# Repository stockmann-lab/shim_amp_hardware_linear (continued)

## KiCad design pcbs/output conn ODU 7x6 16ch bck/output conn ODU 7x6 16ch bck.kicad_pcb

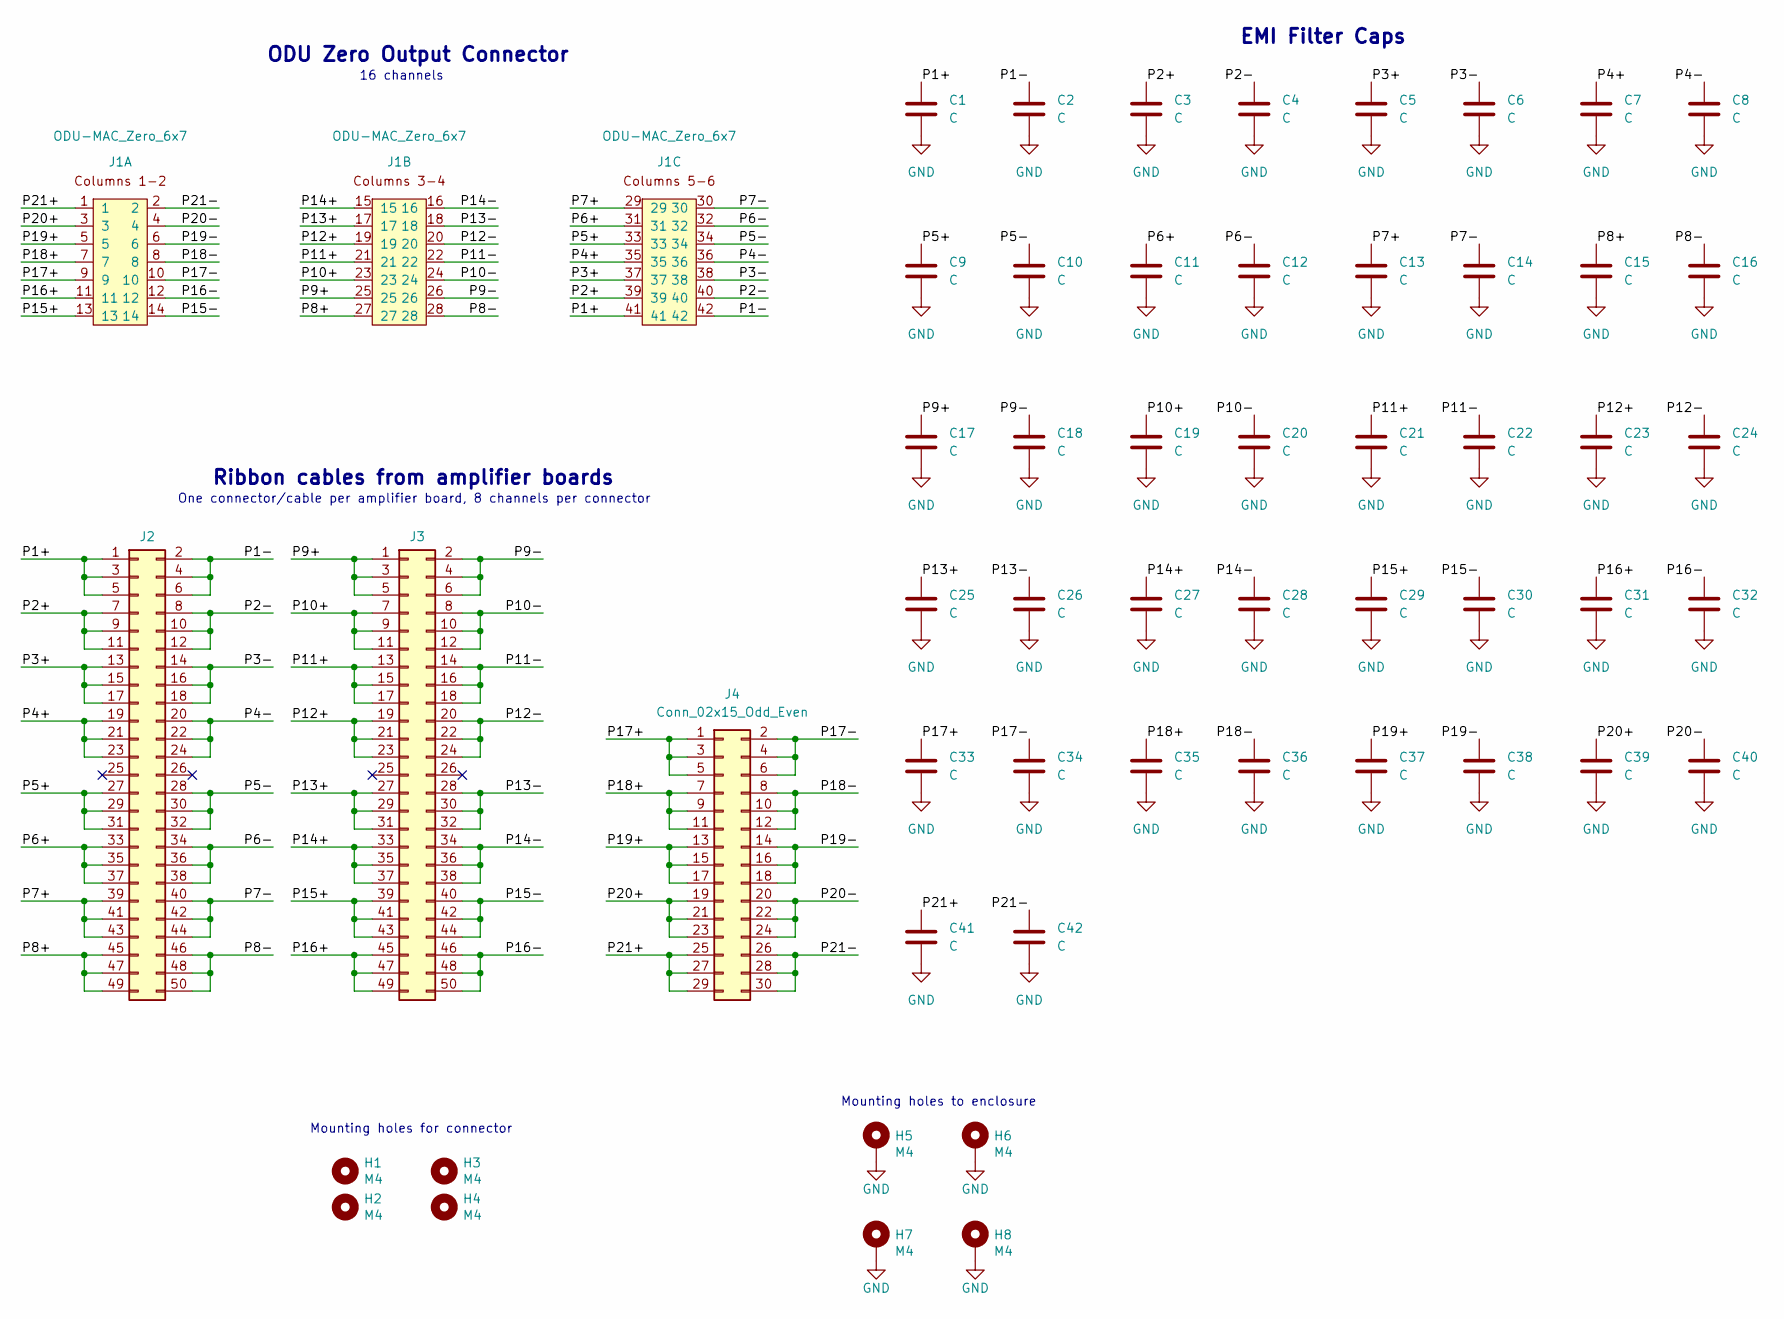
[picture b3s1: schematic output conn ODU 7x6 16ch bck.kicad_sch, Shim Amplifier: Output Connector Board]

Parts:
C1, C2, C3, C4, C5, C6, C7, C8, C9, C10, C11, C12, C13, C14, C15, C16, C17, C18, C19, C20, C21, C22, C23, C24, C25, C26, C27, C28, C29, C30, C31, C32, C33, C34, C35, C36, C37, C38, C39, C40, C41, C42: C; C_0603_1608Metric
H1, H2, H3, H4: M4; MountingHole_4.3mm_M4
H5, H6, H7, H8: M4; MountingHole_4.3mm_M4_Pad_Via
J1: ODU-MAC_Zero_6x7; ODU-MAC_Zero_6x7_bck
J2, J3: Conn_02x25_Odd_Even; PinHeader_2x25_P2.54mm_Vertical_Shrouded
J4: Conn_02x15_Odd_Even; PinHeader_2x15_P2.54mm_Vertical_Shrouded

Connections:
/P1+: C1.1, J1.41, J2.1, J2.3, J2.5
/P1-: C2.1, J1.42, J2.2, J2.4, J2.6
/P2+: C3.1, J1.39, J2.7, J2.9, J2.11
/P2-: C4.1, J1.40, J2.8, J2.10, J2.12
/P3+: C5.1, J1.37, J2.13, J2.15, J2.17
/P3-: C6.1, J1.38, J2.14, J2.16, J2.18
/P4+: C7.1, J1.35, J2.19, J2.21, J2.23
/P4-: C8.1, J1.36, J2.20, J2.22, J2.24
/P5+: C9.1, J1.33, J2.27, J2.29, J2.31
/P5-: C10.1, J1.34, J2.28, J2.30, J2.32
/P6+: C11.1, J1.31, J2.33, J2.35, J2.37
/P6-: C12.1, J1.32, J2.34, J2.36, J2.38
/P7+: C13.1, J1.29, J2.39, J2.41, J2.43
/P7-: C14.1, J1.30, J2.40, J2.42, J2.44
/P8+: C15.1, J1.27, J2.45, J2.47, J2.49
/P8-: C16.1, J1.28, J2.46, J2.48, J2.50
/P9+: C17.1, J1.25, J3.1, J3.3, J3.5
/P9-: C18.1, J1.26, J3.2, J3.4, J3.6
/P10+: C19.1, J1.23, J3.7, J3.9, J3.11
/P10-: C20.1, J1.24, J3.8, J3.10, J3.12
/P11+: C21.1, J1.21, J3.13, J3.15, J3.17
/P11-: C22.1, J1.22, J3.14, J3.16, J3.18
/P12+: C23.1, J1.19, J3.19, J3.21, J3.23
/P12-: C24.1, J1.20, J3.20, J3.22, J3.24
/P13+: C25.1, J1.17, J3.27, J3.29, J3.31
/P13-: C26.1, J1.18, J3.28, J3.30, J3.32
/P14+: C27.1, J1.15, J3.33, J3.35, J3.37
/P14-: C28.1, J1.16, J3.34, J3.36, J3.38
/P15+: C29.1, J1.13, J3.39, J3.41, J3.43
/P15-: C30.1, J1.14, J3.40, J3.42, J3.44
/P16+: C31.1, J1.11, J3.45, J3.47, J3.49
/P16-: C32.1, J1.12, J3.46, J3.48, J3.50
/P17+: C33.1, J1.9, J4.1, J4.3, J4.5
/P17-: C34.1, J1.10, J4.2, J4.4, J4.6
/P18+: C35.1, J1.7, J4.7, J4.9, J4.11
/P18-: C36.1, J1.8, J4.8, J4.10, J4.12
/P19+: C37.1, J1.5, J4.13, J4.15, J4.17
/P19-: C38.1, J1.6, J4.14, J4.16, J4.18
/P20+: C39.1, J1.3, J4.19, J4.21, J4.23
/P20-: C40.1, J1.4, J4.20, J4.22, J4.24
/P21+: C41.1, J1.1, J4.25, J4.27, J4.29
/P21-: C42.1, J1.2, J4.26, J4.28, J4.30
GND: C1.2, C2.2, C3.2, C4.2, C5.2, C6.2, C7.2, C8.2, C9.2, C10.2, C11.2, C12.2, C13.2, C14.2, C15.2, C16.2, C17.2, C18.2, C19.2, C20.2, C21.2, C22.2, C23.2, C24.2, C25.2, C26.2, C27.2, C28.2, C29.2, C30.2, C31.2, C32.2, C33.2, C34.2, C35.2, C36.2, C37.2, C38.2, C39.2, C40.2, C41.2, C42.2, H5.1, H6.1, H7.1, H8.1

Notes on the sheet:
Mounting holes for connector
ODU Zero Output Connector
16 channels
Ribbon cables from amplifier boards
One connector/cable per amplifier board, 8 channels per connector
Mounting holes to enclosure
EMI Filter Caps

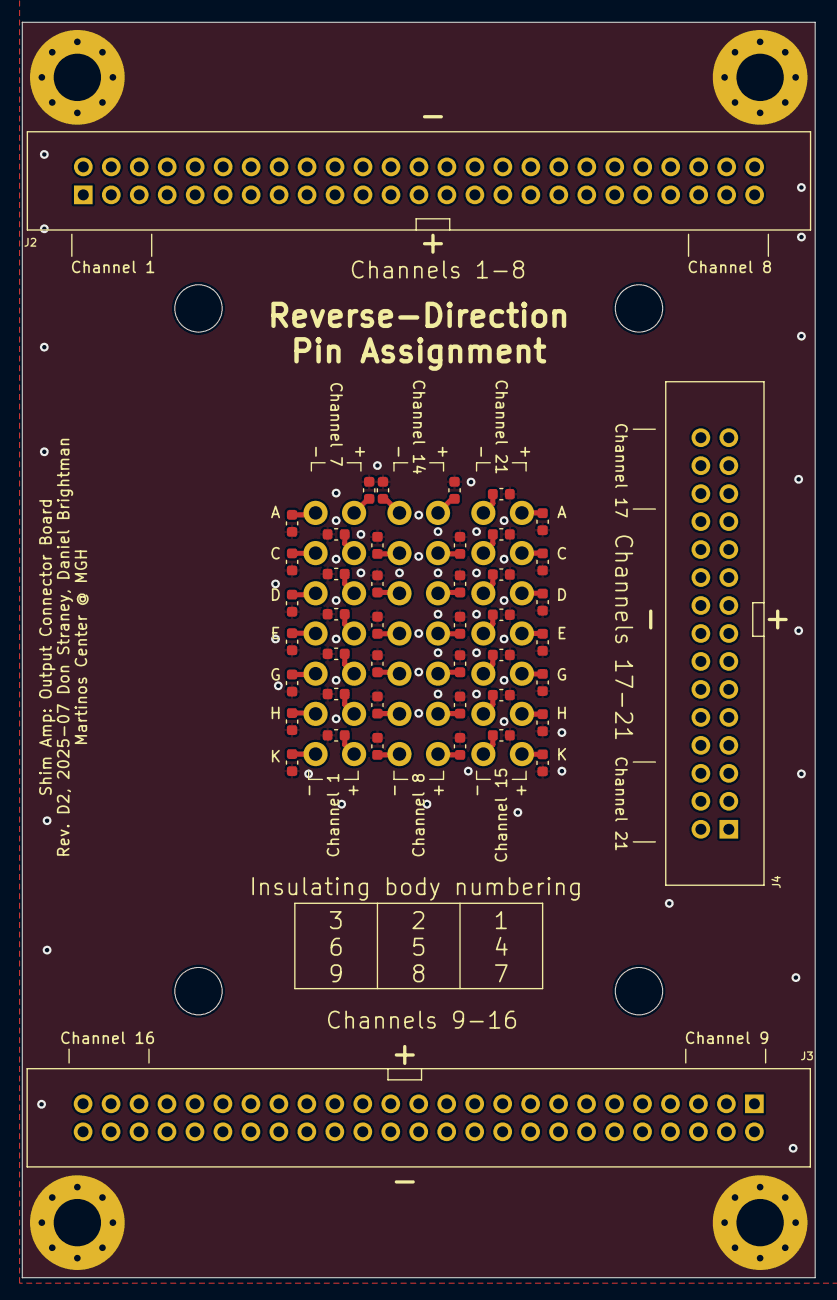
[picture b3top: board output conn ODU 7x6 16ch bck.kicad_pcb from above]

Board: 4 copper layers, 72.0 x 114.0 mm, 54 parts (1 on the bottom side), 43 nets.

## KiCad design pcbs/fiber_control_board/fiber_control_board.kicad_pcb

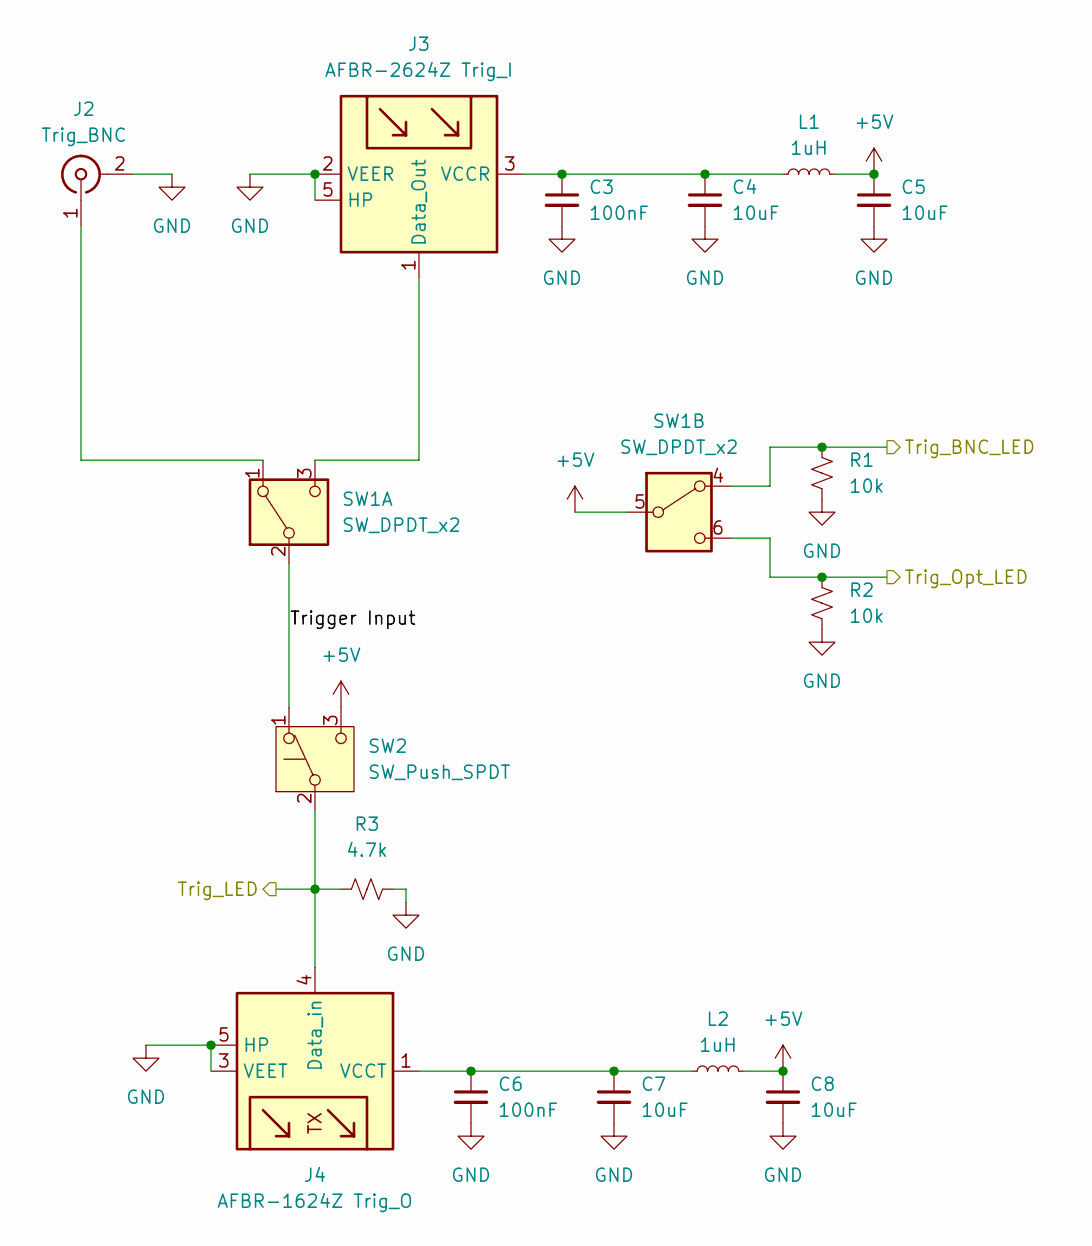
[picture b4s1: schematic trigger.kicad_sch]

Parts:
C3, C6: 100nF; C_0805_2012Metric_Pad1.18x1.45mm_HandSolder
C4, C5, C7, C8: 10uF; C_0805_2012Metric_Pad1.18x1.45mm_HandSolder
J2: Trig_BNC; BNC_panel_and_smd_CONN_CONBN_LNX
J3: AFBR-2624Z Trig_I; AFBR-xx2xZ
J4: AFBR-1624Z Trig_O; AFBR-xx2xZ
L1, L2: 1uH; L_0805_2012Metric_Pad1.15x1.40mm_HandSolder
R1, R2: 10k; R_0805_2012Metric_Pad1.20x1.40mm_HandSolder
R3: 4.7k; R_0805_2012Metric_Pad1.20x1.40mm_HandSolder
SW1: SW_DPDT_x2; DPDT_switch_wires
SW2: SW_Push_SPDT; SPDT_switch_wires

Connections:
+5V: C5.1, C8.1, L1.2, L2.2, SW1.5 (B), SW2.3 (C); also elsewhere on the board
/LEDs/Trig_BNC_LED: R1.1, SW1.4 (A); also elsewhere on the board
/LEDs/Trig_LED: J4.4 (Data_in), R3.1, SW2.2 (B); also elsewhere on the board
/LEDs/Trig_Opt_LED: R2.1, SW1.6 (C); also elsewhere on the board
/Trigger/Trigger Input: SW1.2 (B), SW2.1 (A)
GND: C3.2, C4.2, C5.2, C6.2, C7.2, C8.2, J2.2 (Ext), J3.2 (VEER), J3.5 (HP), J3.8 (HP), J4.3 (VEET), J4.5 (HP), J4.8 (HP), R1.2, R2.2, R3.2; also elsewhere on the board
unnamed: J2.1 (In), SW1.1 (A)
unnamed: J3.1 (Data_Out), SW1.3 (C)
unnamed: C3.1, C4.1, J3.3 (VCCR), L1.1
unnamed: C6.1, C7.1, J4.1 (VCCT), L2.1

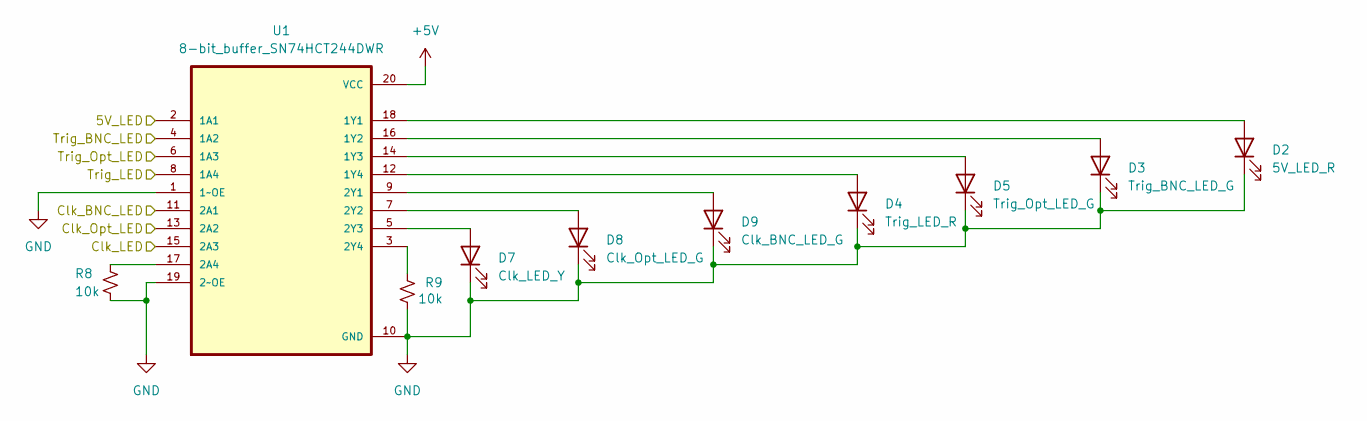
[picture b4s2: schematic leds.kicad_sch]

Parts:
D2: 5V_LED_R; LED_wires
D3: Trig_BNC_LED_G; LED_wires
D4: Trig_LED_R; LED_wires
D5: Trig_Opt_LED_G; LED_wires
D7: Clk_LED_Y; LED_wires
D8: Clk_Opt_LED_G; LED_wires
D9: Clk_BNC_LED_G; LED_wires
R8, R9: 10k; R_0805_2012Metric_Pad1.20x1.40mm_HandSolder
U1: 8-bit_buffer_SN74HCT244DWR

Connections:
+5V: U1.2 (1A1), U1.20 (VCC); also elsewhere on the board
/Clock/Clk_BNC_LED: U1.11 (2A1); also elsewhere on the board
/Clock/Clk_LED: U1.15 (2A3); also elsewhere on the board
/Clock/Clk_Opt_LED: U1.13 (2A2); also elsewhere on the board
/LEDs/Trig_BNC_LED: U1.4 (1A2); also elsewhere on the board
/LEDs/Trig_LED: U1.8 (1A4); also elsewhere on the board
/LEDs/Trig_Opt_LED: U1.6 (1A3); also elsewhere on the board
GND: D2.1 (K), D3.1 (K), D4.1 (K), D5.1 (K), D7.1 (K), D8.1 (K), D9.1 (K), R8.1, R9.2, U1.1 (1~OE), U1.10 (GND), U1.19 (2~OE); also elsewhere on the board
unnamed: D2.2 (A), U1.18 (1Y1)
unnamed: D3.2 (A), U1.16 (1Y2)
unnamed: D4.2 (A), U1.12 (1Y4)
unnamed: D5.2 (A), U1.14 (1Y3)
unnamed: D7.2 (A), U1.5 (2Y3)
unnamed: D8.2 (A), U1.7 (2Y2)
unnamed: D9.2 (A), U1.9 (2Y1)
unnamed: R8.2, U1.17 (2A4)
unnamed: R9.1, U1.3 (2Y4)

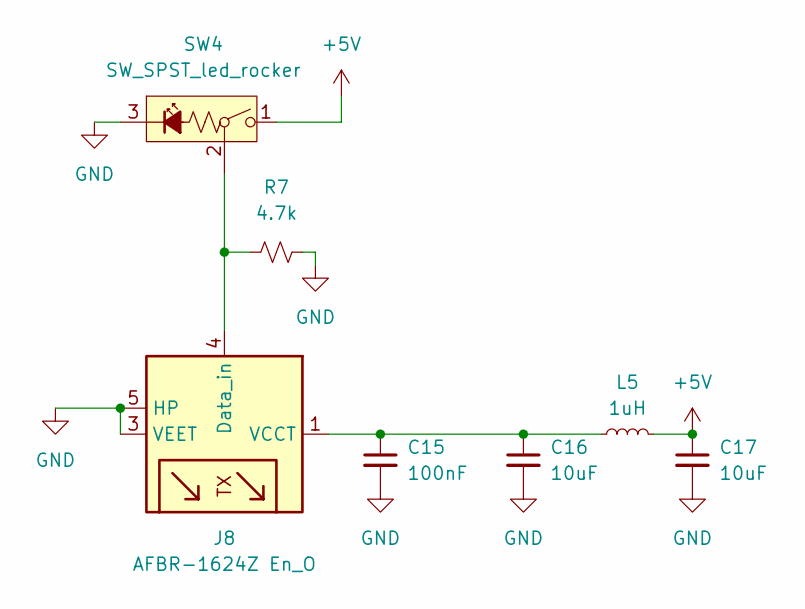
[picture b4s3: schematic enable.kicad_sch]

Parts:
C15: 100nF; C_0805_2012Metric_Pad1.18x1.45mm_HandSolder
C16, C17: 10uF; C_0805_2012Metric_Pad1.18x1.45mm_HandSolder
J8: AFBR-1624Z En_O; AFBR-xx2xZ
L5: 1uH; L_0805_2012Metric_Pad1.15x1.40mm_HandSolder
R7: 4.7k; R_0805_2012Metric_Pad1.20x1.40mm_HandSolder
SW4: SW_SPST_led_rocker; SPST_led_rocker

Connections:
+5V: C17.1, L5.2, SW4.1 (A); also elsewhere on the board
GND: C15.2, C16.2, C17.2, J8.3 (VEET), J8.5 (HP), J8.8 (HP), R7.2, SW4.3 (C); also elsewhere on the board
unnamed: J8.4 (Data_in), R7.1, SW4.2 (B)
unnamed: C15.1, C16.1, J8.1 (VCCT), L5.1

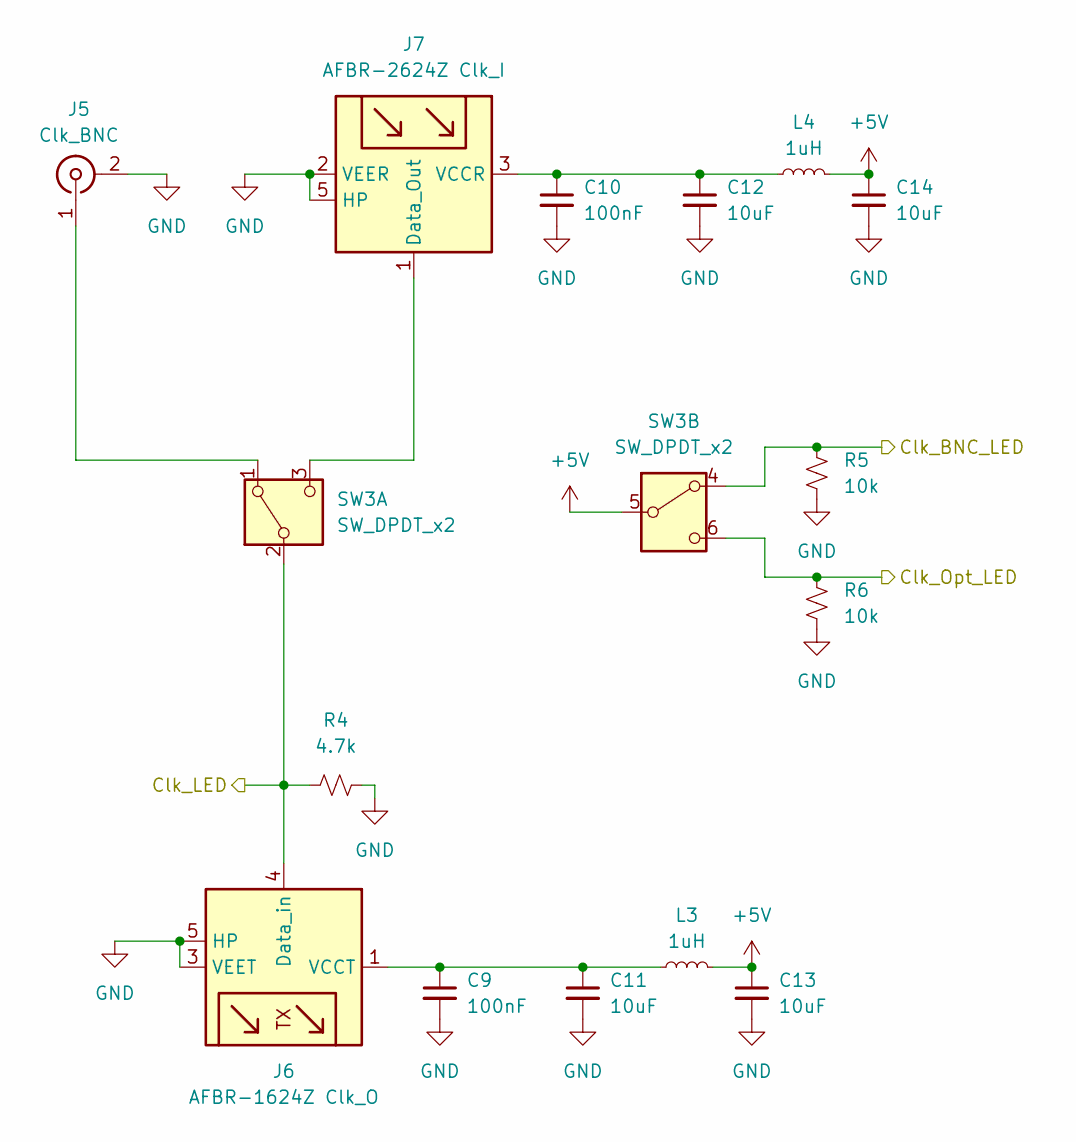
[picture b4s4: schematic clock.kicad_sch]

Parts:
C9, C10: 100nF; C_0805_2012Metric_Pad1.18x1.45mm_HandSolder
C11, C12, C13, C14: 10uF; C_0805_2012Metric_Pad1.18x1.45mm_HandSolder
J5: Clk_BNC; BNC_panel_and_smd_CONN_CONBN_LNX
J6: AFBR-1624Z Clk_O; AFBR-xx2xZ
J7: AFBR-2624Z Clk_I; AFBR-xx2xZ
L3, L4: 1uH; L_0805_2012Metric_Pad1.15x1.40mm_HandSolder
R4: 4.7k; R_0805_2012Metric_Pad1.20x1.40mm_HandSolder
R5, R6: 10k; R_0805_2012Metric_Pad1.20x1.40mm_HandSolder
SW3: SW_DPDT_x2; DPDT_switch_wires

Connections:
+5V: C13.1, C14.1, L3.2, L4.2, SW3.5 (B); also elsewhere on the board
/Clock/Clk_BNC_LED: R5.1, SW3.4 (A); also elsewhere on the board
/Clock/Clk_LED: J6.4 (Data_in), R4.1, SW3.2 (B); also elsewhere on the board
/Clock/Clk_Opt_LED: R6.1, SW3.6 (C); also elsewhere on the board
GND: C9.2, C10.2, C11.2, C12.2, C13.2, C14.2, J5.2 (Ext), J6.3 (VEET), J6.5 (HP), J6.8 (HP), J7.2 (VEER), J7.5 (HP), J7.8 (HP), R4.2, R5.2, R6.2; also elsewhere on the board
unnamed: J5.1 (In), SW3.1 (A)
unnamed: C9.1, C11.1, J6.1 (VCCT), L3.1
unnamed: J7.1 (Data_Out), SW3.3 (C)
unnamed: C10.1, C12.1, J7.3 (VCCR), L4.1

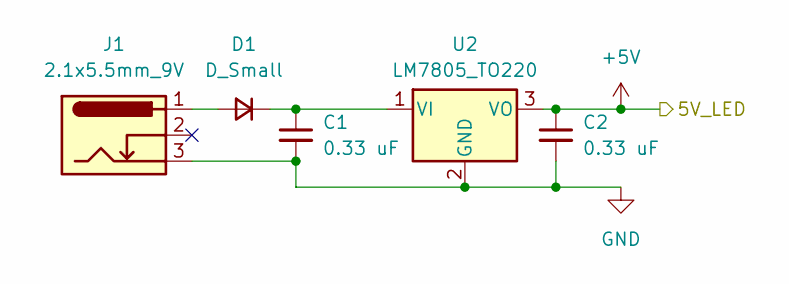
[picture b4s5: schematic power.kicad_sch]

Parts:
C1, C2: 0.33 uF; C_0805_2012Metric_Pad1.18x1.45mm_HandSolder
D1: D_Small; D_0805_2012Metric_Pad1.15x1.40mm_HandSolder
J1: 2.1x5.5mm_9V; Barrel_Jack_CONN3_54-00166_TEN
U2: LM7805_TO220; MC7805CTG_with_heatsink_

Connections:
+5V: C2.1, U2.3 (VO); also elsewhere on the board
GND: C1.2, C2.2, J1.3, U2.2 (GND); also elsewhere on the board
unnamed: D1.2 (A), J1.1
unnamed: C1.1, D1.1 (K), U2.1 (VI)

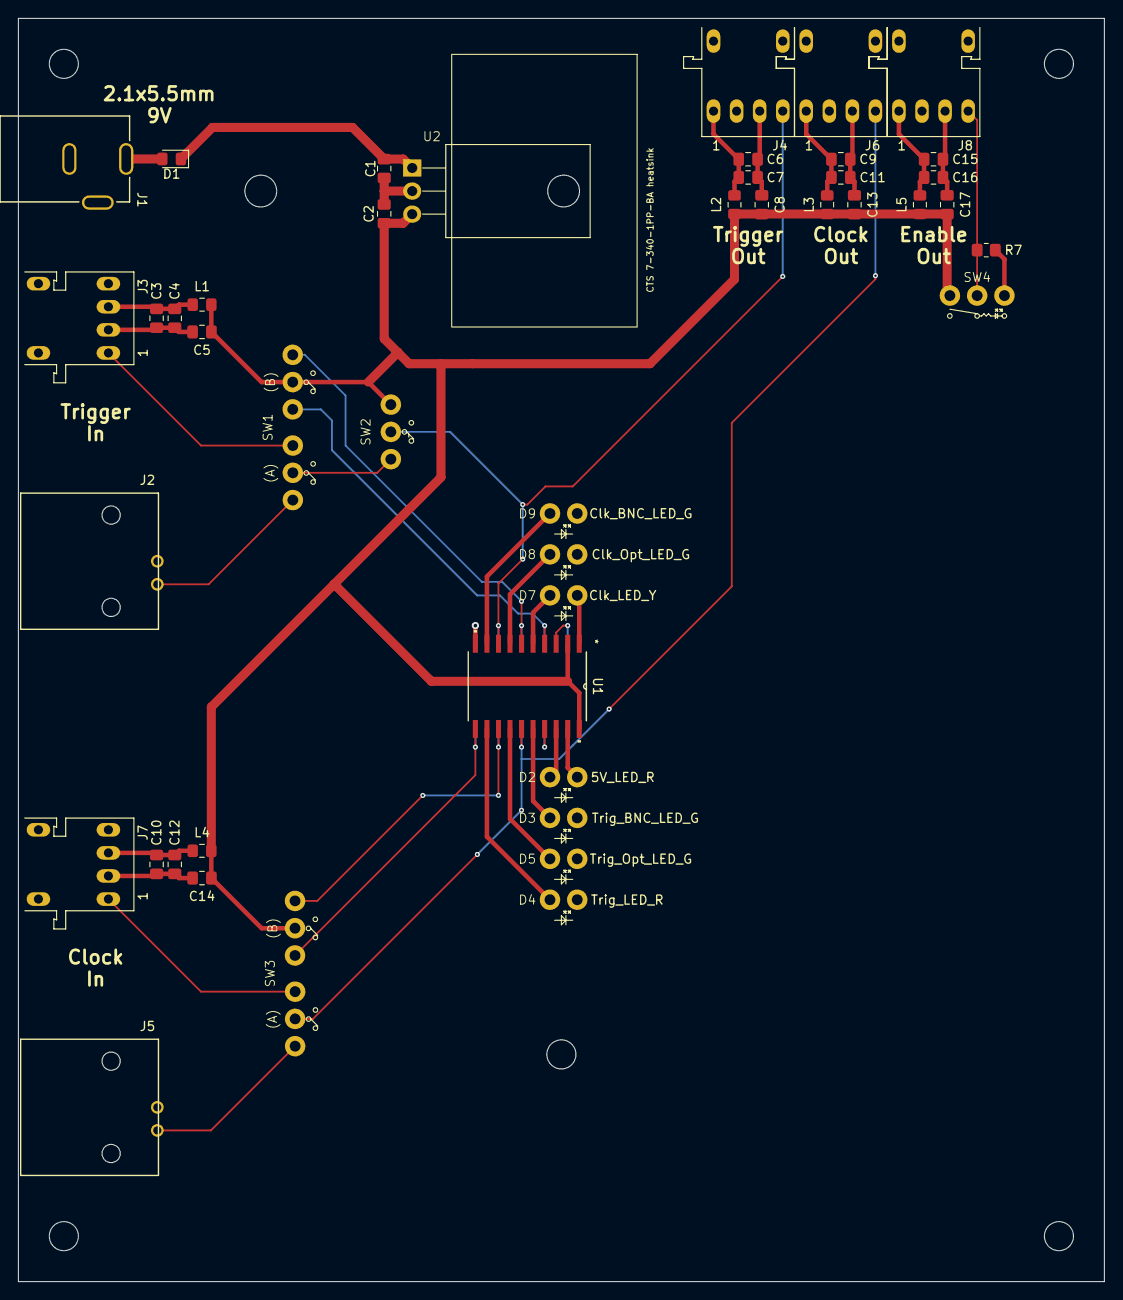
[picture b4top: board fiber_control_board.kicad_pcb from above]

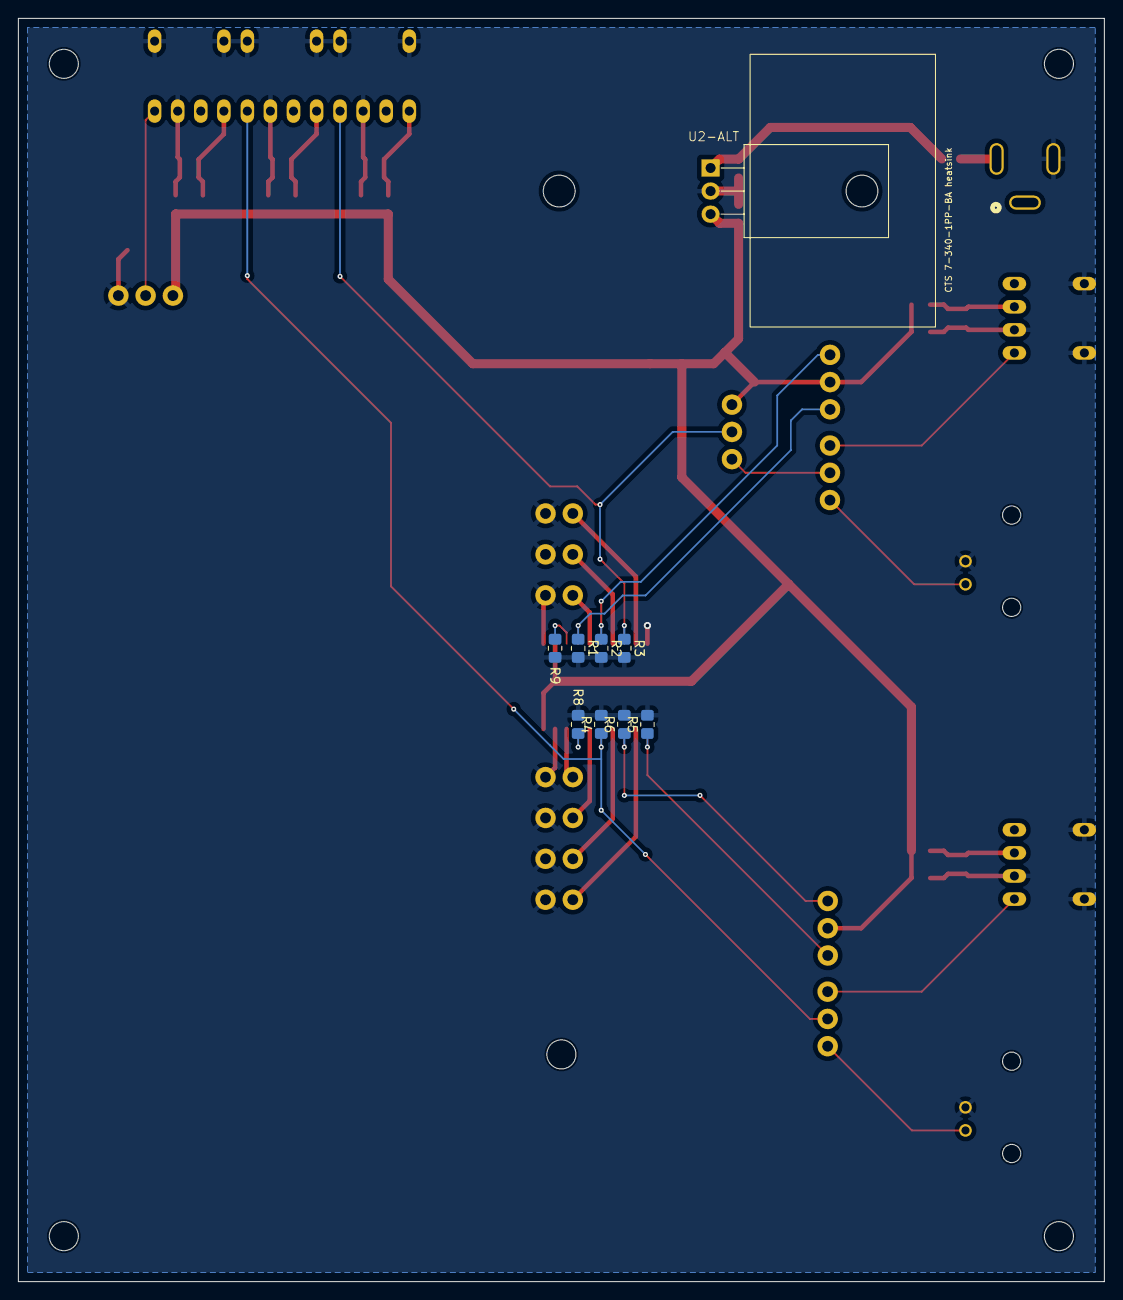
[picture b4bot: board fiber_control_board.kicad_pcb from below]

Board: 2 copper layers, 119.5 x 139.0 mm, 54 parts (9 on the bottom side), 30 nets.

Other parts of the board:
U2-ALT: LM7805_TO220; MC7805CTG_with_heatsink_

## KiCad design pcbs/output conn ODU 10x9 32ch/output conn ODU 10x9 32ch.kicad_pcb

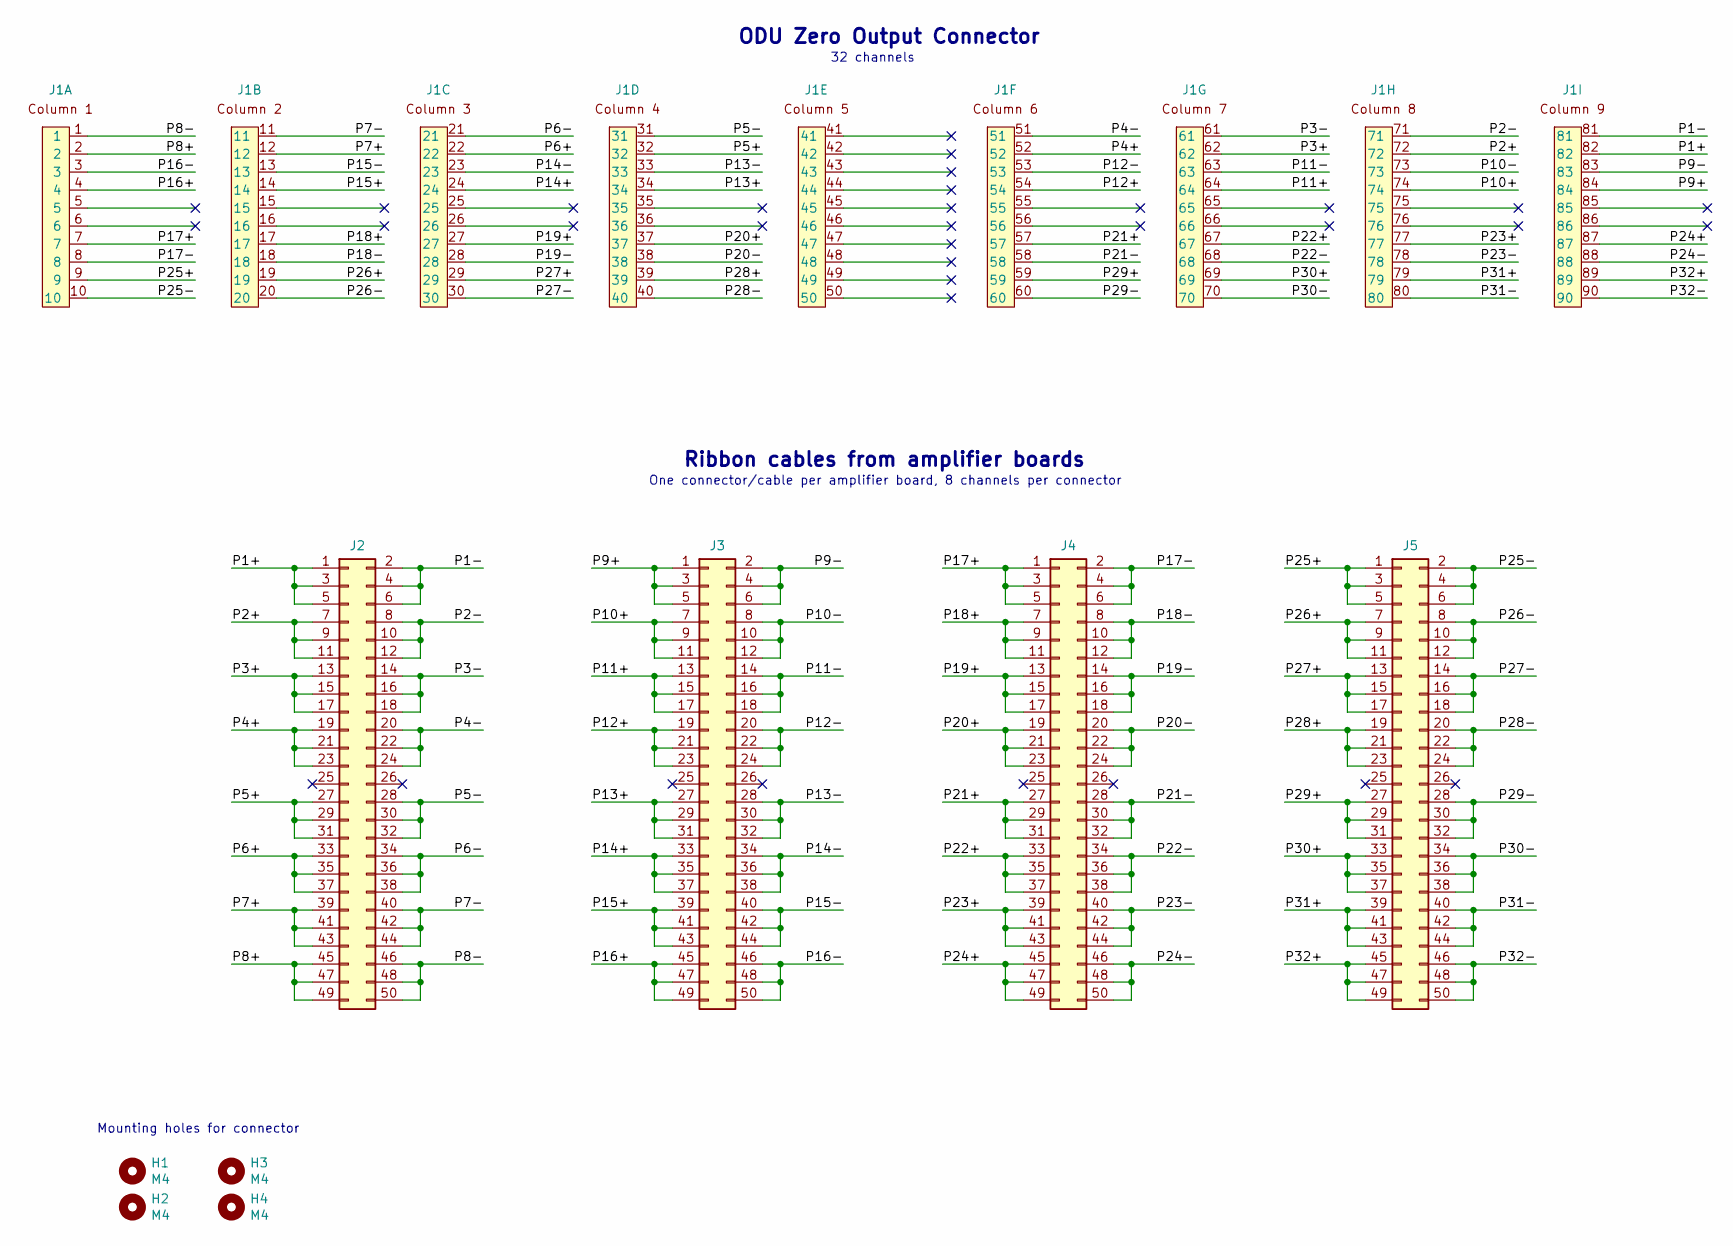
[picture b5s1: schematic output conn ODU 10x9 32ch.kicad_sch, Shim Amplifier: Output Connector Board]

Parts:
H1, H2, H3, H4: M4; MountingHole_4.3mm_M4
J1: ODU-MAC_Zero_10x9
J2, J3, J4, J5: Conn_02x25_Odd_Even; PinHeader_2x25_P2.54mm_Vertical_Shrouded

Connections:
/P1+: J1.82, J2.1, J2.3, J2.5
/P1-: J1.81, J2.2, J2.4, J2.6
/P2+: J1.72, J2.7, J2.9, J2.11
/P2-: J1.71, J2.8, J2.10, J2.12
/P3+: J1.62, J2.13, J2.15, J2.17
/P3-: J1.61, J2.14, J2.16, J2.18
/P4+: J1.52, J2.19, J2.21, J2.23
/P4-: J1.51, J2.20, J2.22, J2.24
/P5+: J1.32, J2.27, J2.29, J2.31
/P5-: J1.31, J2.28, J2.30, J2.32
/P6+: J1.22, J2.33, J2.35, J2.37
/P6-: J1.21, J2.34, J2.36, J2.38
/P7+: J1.12, J2.39, J2.41, J2.43
/P7-: J1.11, J2.40, J2.42, J2.44
/P8+: J1.2, J2.45, J2.47, J2.49
/P8-: J1.1, J2.46, J2.48, J2.50
/P9+: J1.84, J3.1, J3.3, J3.5
/P9-: J1.83, J3.2, J3.4, J3.6
/P10+: J1.74, J3.7, J3.9, J3.11
/P10-: J1.73, J3.8, J3.10, J3.12
/P11+: J1.64, J3.13, J3.15, J3.17
/P11-: J1.63, J3.14, J3.16, J3.18
/P12+: J1.54, J3.19, J3.21, J3.23
/P12-: J1.53, J3.20, J3.22, J3.24
/P13+: J1.34, J3.27, J3.29, J3.31
/P13-: J1.33, J3.28, J3.30, J3.32
/P14+: J1.24, J3.33, J3.35, J3.37
/P14-: J1.23, J3.34, J3.36, J3.38
/P15+: J1.14, J3.39, J3.41, J3.43
/P15-: J1.13, J3.40, J3.42, J3.44
/P16+: J1.4, J3.45, J3.47, J3.49
/P16-: J1.3, J3.46, J3.48, J3.50
/P17+: J1.7, J4.1, J4.3, J4.5
/P17-: J1.8, J4.2, J4.4, J4.6
/P18+: J1.17, J4.7, J4.9, J4.11
/P18-: J1.18, J4.8, J4.10, J4.12
/P19+: J1.27, J4.13, J4.15, J4.17
/P19-: J1.28, J4.14, J4.16, J4.18
/P20+: J1.37, J4.19, J4.21, J4.23
/P20-: J1.38, J4.20, J4.22, J4.24
/P21+: J1.57, J4.27, J4.29, J4.31
/P21-: J1.58, J4.28, J4.30, J4.32
/P22+: J1.67, J4.33, J4.35, J4.37
/P22-: J1.68, J4.34, J4.36, J4.38
/P23+: J1.77, J4.39, J4.41, J4.43
/P23-: J1.78, J4.40, J4.42, J4.44
/P24+: J1.87, J4.45, J4.47, J4.49
/P24-: J1.88, J4.46, J4.48, J4.50
/P25+: J1.9, J5.1, J5.3, J5.5
/P25-: J1.10, J5.2, J5.4, J5.6
/P26+: J1.19, J5.7, J5.9, J5.11
/P26-: J1.20, J5.8, J5.10, J5.12
/P27+: J1.29, J5.13, J5.15, J5.17
/P27-: J1.30, J5.14, J5.16, J5.18
/P28+: J1.39, J5.19, J5.21, J5.23
/P28-: J1.40, J5.20, J5.22, J5.24
/P29+: J1.59, J5.27, J5.29, J5.31
/P29-: J1.60, J5.28, J5.30, J5.32
/P30+: J1.69, J5.33, J5.35, J5.37
/P30-: J1.70, J5.34, J5.36, J5.38
/P31+: J1.79, J5.39, J5.41, J5.43
/P31-: J1.80, J5.40, J5.42, J5.44
/P32+: J1.89, J5.45, J5.47, J5.49
/P32-: J1.90, J5.46, J5.48, J5.50

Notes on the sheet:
ODU Zero Output Connector
32 channels
Mounting holes for connector
One connector/cable per amplifier board, 8 channels per connector
Ribbon cables from amplifier boards

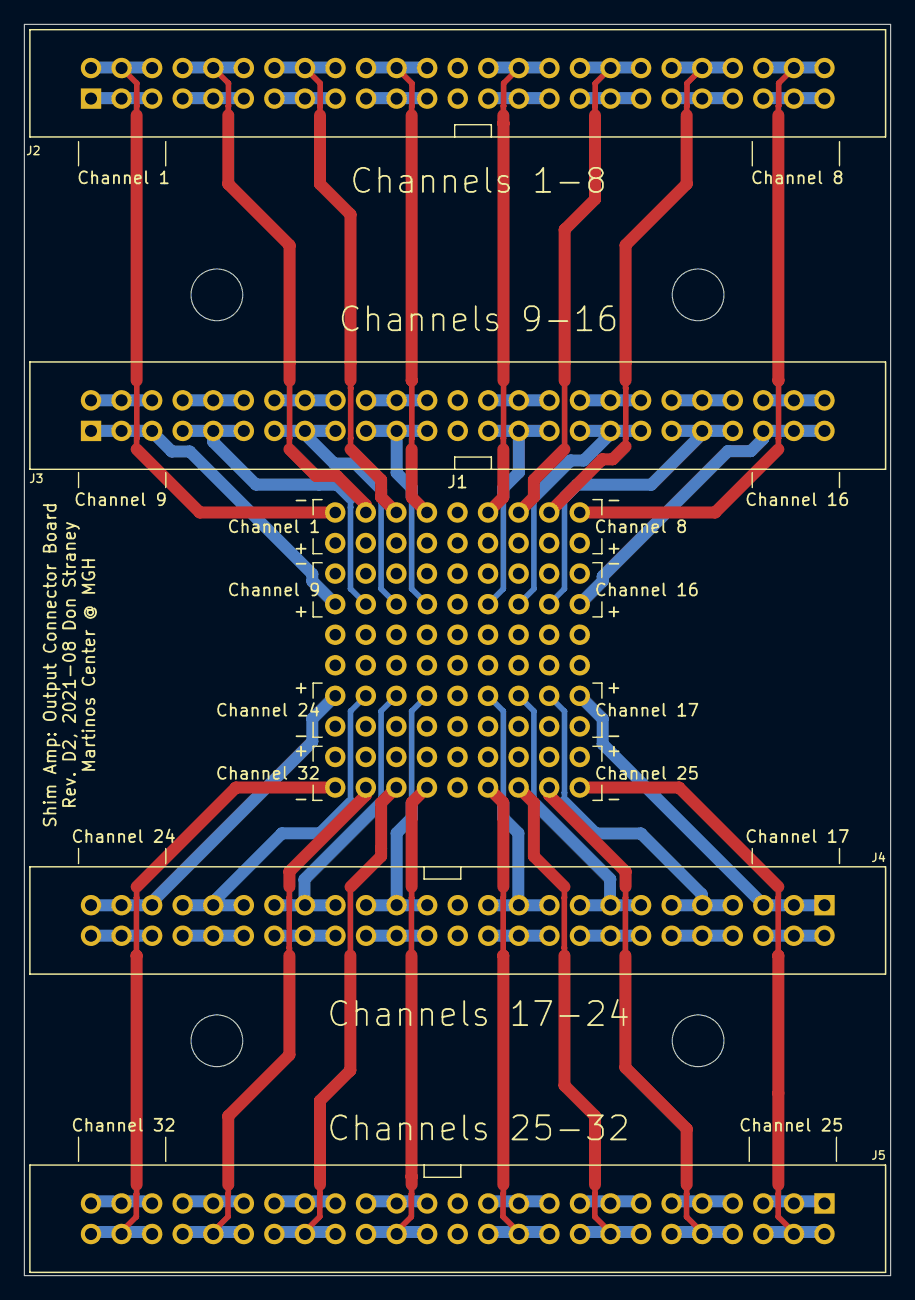
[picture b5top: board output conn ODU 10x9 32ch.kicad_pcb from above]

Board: 4 copper layers, 72.0 x 104.0 mm, 9 parts (1 on the bottom side), 64 nets.
